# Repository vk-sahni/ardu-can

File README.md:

# Ardu-CAN

Ardu-CAN is a compact embedded-controller PCB design portfolio built in KiCad.
It brings together an STM32F412 MCU, CAN-bus interface circuitry, an inertial
sensor, power-protection and regulation circuits, and a custom board layout.

Explore the editable KiCad design, project libraries, engineering exports, and
3D assembly model below. The repository also documents the current design
review and next steps toward a fabrication release.

> **Board identity:** the PCB silkscreen currently says `Can-Glove-Node`.
> `Ardu-CAN` is the portfolio/project name used in this repository.

## Contents

- [Project objectives](#project-objectives)
- [Verified hardware features](#verified-hardware-features)
- [Hardware architecture](#hardware-architecture)
- [PCB design overview](#pcb-design-overview)
- [Schematic and engineering exports](#schematic-and-engineering-exports)
- [3D model](#3d-model)
- [Engineering review and release status](#engineering-review-and-release-status)
- [Open the project in KiCad](#open-the-project-in-kicad)
- [Commercial design services](#commercial-design-services)
- [Licensing and third-party assets](#licensing-and-third-party-assets)

## Project objectives

The project brings together an STM32 microcontroller, a CAN physical-layer
interface, an inertial measurement component, power input protection, and
connectors on a custom PCB. It demonstrates schematic capture, component and
footprint selection, board placement and routing, local KiCad library assets,
and 3D assembly export.

This portfolio focuses on the hardware design and its engineering assets.
Firmware and system-level behavior can be scoped separately for projects that
need them.

## Verified hardware features

The following parts and design elements were confirmed in the checked-in
schematic/PCB data and the KiCad BOM export:

| Design element | Verified implementation |
| --- | --- |
| Main MCU | U8, `STM32F412CGUx`, in a 48-pin QFN footprint |
| CAN physical layer | U5, `TJA1051TK-3` CAN transceiver; J1 and J2 are labeled `CAN` |
| CAN protection | D1 is `NUP2105L`; ESD9C3.3ST5G protection components also appear in the design |
| Inertial sensor | U4, `ICM-42688-P` |
| 3.3 V regulator | U6, `NCV8705MT33TCG` |
| Input protection | U1, `LM66100DCK`, on the reverse-polarity-protection sheet |
| Clock component | X1, `LFSPXO072801REEL` |
| Connections | JST GH/SH connectors and headers, including two 4-pin connectors labeled `CAN` |
| Test access | Three test-point footprints are present in the exported BOM |

The STM32F412 family datasheet lists an on-chip bxCAN controller
([STMicroelectronics datasheet](https://www.st.com/resource/en/datasheet/stm32f412cg.pdf));
U5 is the separate TJA1051 physical-layer transceiver. The schematic therefore
contains both controller-capable MCU hardware and a CAN transceiver, but the
repository has no firmware or test evidence establishing bus operation,
bit-rate, termination behavior, or protocol-level performance.

The schematic also contains passives, fuses, LEDs, and other protection
components. Part ratings, exact connector pin assignments, supported CAN
bit-rates, sensor configuration, and system behavior must be confirmed against
the detailed design and component datasheets before use.

## Hardware architecture

The KiCad schematic is organized into these sheets:

- `REVERSE_POLARITY_PROTECTION`
- `POWER_SUPPLY`
- `3.3_REGULATOR`
- `STM32`
- `CAN_DRIVER`
- `Accel`
- `CONNECTORS`

The exported schematic PDF includes the hierarchy page and all seven circuit
sheets. Current electrical review findings are summarized in the validation
section below.

## PCB design overview

- Nominal board outline: **37 × 37 mm**, as drawn on `Edge.Cuts`.
- Configured board thickness: **1.6 mm**.
- Configured copper stackup: **six copper layers** (front, four inner layers,
  and back).
- The outline contains four circular, nominal 3 mm diameter `Edge.Cuts`
  features. Confirm their intended use and mechanical clearances in the final
  enclosure and fabrication review.
- The source PCB contains 82 footprints and routed copper. This count is from
  the board file and is not an assembly or production status.

## Schematic and engineering exports

The schematic illustration below shows the actual KiCad CAN-driver sheet with
a summary of other verified blocks. For readable circuit detail, use the full
PDF rather than relying on the thumbnail.

- [Full eight-page schematic PDF](docs/ardu-can-schematic.pdf)
- [KiCad-exported BOM CSV](docs/ardu-can-bom.csv)
- Editable root schematic: [`ardu-can.kicad_sch`](ardu-can.kicad_sch)
- Editable board: [`ardu-can.kicad_pcb`](ardu-can.kicad_pcb)
- KiCad project settings: [`ardu-can.kicad_pro`](ardu-can.kicad_pro)
- Project symbol/footprint tables: [`sym-lib-table`](sym-lib-table) and
  [`fp-lib-table`](fp-lib-table)
- Custom and supporting KiCad libraries: [`lib/`](lib/)
- Component 3D models used by the project: [`model/`](model/)

The CSV is an exported design BOM, not a fully sourced purchasing BOM: supplier
part numbers, lifecycle checks, alternates, and procurement verification are
not established by that export.

## 3D model

The repository includes a KiCad-generated STEP assembly model. The image below
shows KiCad renders from multiple board views; it is not a photograph of a
fabricated or assembled unit.

- [Assembly STEP model](3d/ardu-can-assembly.step)
- [KiCad component model assets](model/)

The STEP file is an export of the current design data. No independent
mechanical fit, enclosure, or third-party CAD validation is claimed.

## Engineering review and release status

The project has editable KiCad design files and exported engineering assets.
Use the validation review to plan the next engineering steps before fabrication.

<details>
<summary>View current ERC/DRC findings and release checks</summary>

- The KiCad 10.0.6 PCB DRC reports **458 violations**, including via diameter
  and annular-width findings, library-footprint mismatches, clearance and
  copper-to-edge findings, silkscreen/courtyard issues, dangling tracks, and
  one unconnected item.
- The schematic ERC reports **61 violations**: 11 errors and 50 warnings.
  Findings include hierarchical sheet-pin/label mismatches, undriven power
  pins, and pin-type warnings.
- The source includes project-specific symbol and footprint tables, but the
  current checks still report footprint-library association/mismatch issues.
- No Gerber, drill, pick-and-place, or fabrication job output files are
  included.
- No fabricated-board, assembly, electrical bench test, or firmware validation
  evidence is included.

The detailed [design review](docs/design-review.md), [PCB DRC report](docs/pcb-drc-report.txt),
and [schematic ERC report](docs/schematic-erc-report.txt) provide the exact
findings. The release workflow is to resolve and rerun ERC/DRC, verify library
associations and footprint assignments, check the outline, holes, connector
mating clearances, enclosure fit, stack-up, and fabricator capabilities, then
generate and inspect Gerber/drill outputs and complete a sourced BOM as needed.

</details>

## Open the project in KiCad

1. Use **KiCad 10** (the checked CLI version for the exports and checks in this
   repository was 10.0.6).
2. Open `ardu-can.kicad_pro` from the repository root.
3. Open the root schematic or PCB editor from the project manager.
4. Keep the `lib/` and `model/` folders in their current relative locations:
   the project tables and footprints use project-relative library/model paths.
5. Review the current ERC/DRC findings before editing or preparing fabrication
   data.

Opening the project in another KiCad version may prompt a file-format upgrade.
Make a separate copy before accepting a project-wide upgrade.

## Commercial design services

This project is a portfolio example of the kinds of schematic, PCB layout,
component/footprint, and 3D STEP work available as a custom service. It does not
establish that every feature in a future client design is included, tested, or
certified.

The service scope, revision allowance, source files, manufacturing outputs,
firmware, and testing are defined per project and agreed package. Fabrication,
assembly, firmware development, and physical testing are not included unless
explicitly agreed.

See the [Fiverr listing and packages](docs/fiverr-gig.md) for service details.

## Licensing and third-party assets

No blanket project license is included because the repository combines original
design files with library/model assets that may have separate license terms.
The ICM-42688-P library folder includes its own `License.txt`; retain and review
third-party notices before redistribution or commercial reuse. Agree ownership
and licensing for client deliverables in writing before work begins.

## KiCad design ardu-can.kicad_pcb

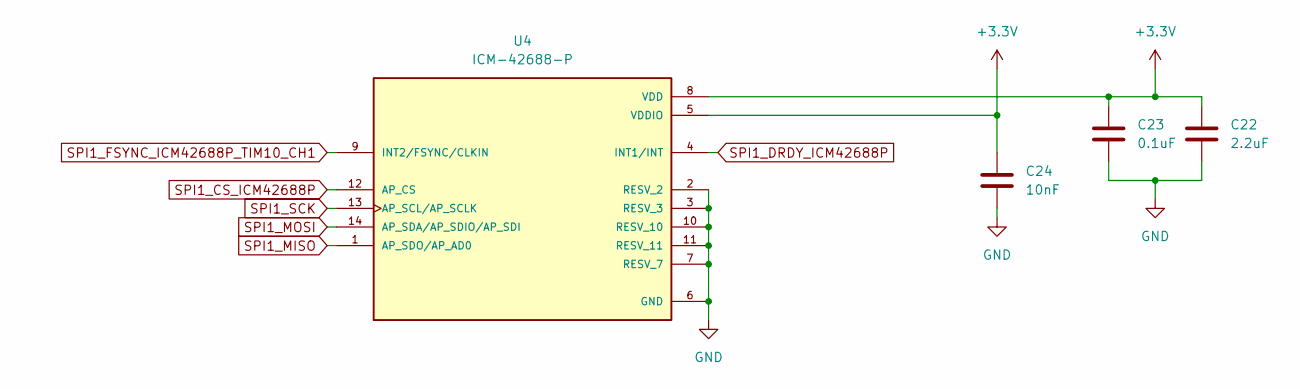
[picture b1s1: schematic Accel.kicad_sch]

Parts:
C22: 2.2uF; C_0603_1608Metric_Pad1.08x0.95mm_HandSolder
C23: 0.1uF; C_0603_1608Metric_Pad1.08x0.95mm_HandSolder
C24: 10nF; C_0603_1608Metric_Pad1.08x0.95mm_HandSolder
U4: ICM-42688-P; PQFN50P300X250X97-14N; PARTREV 1.2

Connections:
+3.3V: C22.1, C23.1, C24.1, U4.5 (VDDIO), U4.8 (VDD); also elsewhere on the board
GND: C22.2, C23.2, C24.2, U4.2 (RESV_2), U4.3 (RESV_3), U4.6 (GND), U4.7 (RESV_7), U4.10 (RESV_10), U4.11 (RESV_11); also elsewhere on the board
SPI1_CS_ICM42688P: U4.12 (AP_CS); also elsewhere on the board
SPI1_DRDY_ICM42688P: U4.4 (INT1/INT); also elsewhere on the board
SPI1_FSYNC_ICM42688P_TIM10_CH1: U4.9 (INT2/FSYNC/CLKIN); also elsewhere on the board
SPI1_MISO: U4.1 (AP_SDO/AP_AD0); also elsewhere on the board
SPI1_MOSI: U4.14 (AP_SDA/AP_SDIO/AP_SDI); also elsewhere on the board
SPI1_SCK: U4.13 (AP_SCL/AP_SCLK); also elsewhere on the board

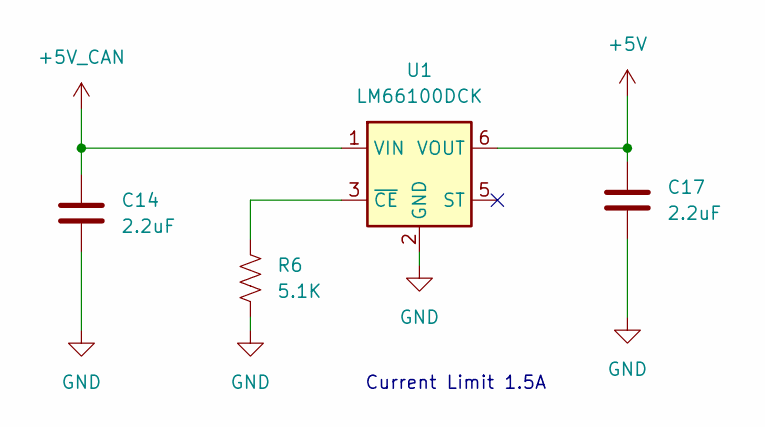
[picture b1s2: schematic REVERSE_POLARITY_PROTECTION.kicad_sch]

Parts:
C14, C17: 2.2uF; C_0603_1608Metric_Pad1.08x0.95mm_HandSolder
R6: 5.1K; R_0603_1608Metric_Pad0.98x0.95mm_HandSolder
U1: LM66100DCK; SOT-363_SC-70-6

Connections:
+5V: C17.1, U1.6 (VOUT); also elsewhere on the board
+5V_CAN: C14.1, U1.1 (VIN); also elsewhere on the board
GND: C14.2, C17.2, R6.2, U1.2 (GND); also elsewhere on the board
unnamed: R6.1, U1.3 (~CE)

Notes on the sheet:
Current Limit 1.5A

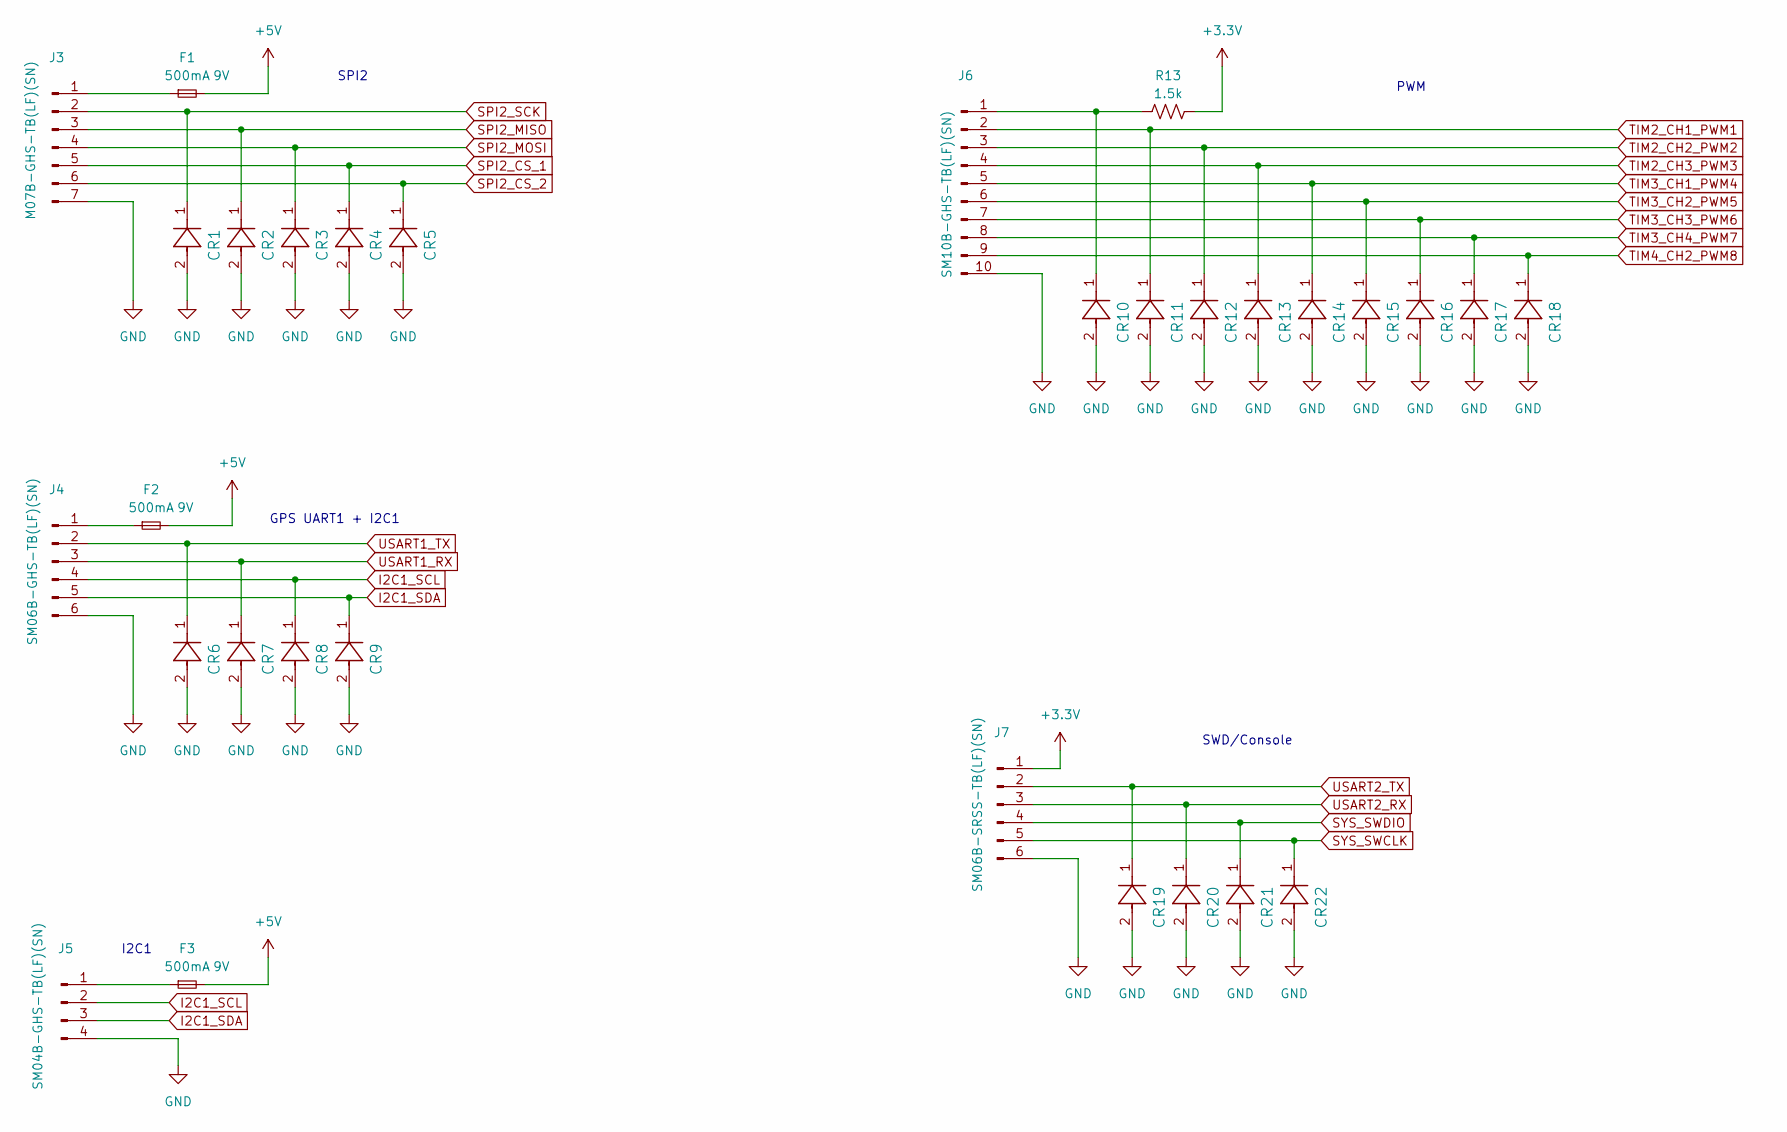
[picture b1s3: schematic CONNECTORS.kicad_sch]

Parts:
CR1, CR2, CR3, CR4, CR5, CR6, CR7, CR8, CR9, CR10, CR11, CR12, CR13, CR14, CR15, CR16, CR17, CR18, CR19, CR20, CR21, CR22: ESD9C3.3ST5G; CR_ESD9C3.3ST5G_ONS
F1, F2, F3: 500mA; Fuse_0603_1608Metric_Pad1.05x0.95mm_HandSolder
J3: M07B-GHS-TB(LF)(SN); JST_GH_SM07B-GHS-TB_1x07-1MP_P1.25mm_Horizontal
J4: SM06B-GHS-TB(LF)(SN); JST_GH_SM06B-GHS-TB_1x06-1MP_P1.25mm_Horizontal
J5: SM04B-GHS-TB(LF)(SN); JST_GH_SM04B-GHS-TB_1x04-1MP_P1.25mm_Horizontal
J6: SM10B-GHS-TB(LF)(SN); JST_GH_SM10B-GHS-TB_1x10-1MP_P1.25mm_Horizontal
J7: SM06B-SRSS-TB(LF)(SN); JST_SH_SM06B-SRSS-TB_1x06-1MP_P1.00mm_Horizontal
R13: 1.5k; R_0603_1608Metric_Pad0.98x0.95mm_HandSolder

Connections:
+3.3V: J7.1, R13.2; also elsewhere on the board
+5V: F1.2, F2.2, F3.2; also elsewhere on the board
GND: CR1.2, CR2.2, CR3.2, CR4.2, CR5.2, CR6.2, CR7.2, CR8.2, CR9.2, CR10.2, CR11.2, CR12.2, CR13.2, CR14.2, CR15.2, CR16.2, CR17.2, CR18.2, CR19.2, CR20.2, CR21.2, CR22.2, J3.7, J4.6, J5.4, J6.10, J7.6; also elsewhere on the board
I2C1_SCL: CR8.1, J4.4, J5.2; also elsewhere on the board
I2C1_SDA: CR9.1, J4.5, J5.3; also elsewhere on the board
unnamed: F1.1, J3.1
unnamed: F2.1, J4.1
unnamed: F3.1, J5.1
unnamed: CR10.1, J6.1, R13.1
SPI2_CS_1: CR4.1, J3.5; also elsewhere on the board
SPI2_CS_2: CR5.1, J3.6; also elsewhere on the board
SPI2_MISO: CR2.1, J3.3; also elsewhere on the board
SPI2_MOSI: CR3.1, J3.4; also elsewhere on the board
SPI2_SCK: CR1.1, J3.2; also elsewhere on the board
SYS_SWCLK: CR22.1, J7.5; also elsewhere on the board
SYS_SWDIO: CR21.1, J7.4; also elsewhere on the board
TIM2_CH1_PWM1: CR11.1, J6.2; also elsewhere on the board
TIM2_CH2_PWM2: CR12.1, J6.3; also elsewhere on the board
TIM2_CH3_PWM3: CR13.1, J6.4; also elsewhere on the board
TIM3_CH1_PWM4: CR14.1, J6.5; also elsewhere on the board
TIM3_CH2_PWM5: CR15.1, J6.6; also elsewhere on the board
TIM3_CH3_PWM6: CR16.1, J6.7; also elsewhere on the board
TIM3_CH4_PWM7: CR17.1, J6.8; also elsewhere on the board
TIM4_CH2_PWM8: CR18.1, J6.9; also elsewhere on the board
USART1_RX: CR7.1, J4.3; also elsewhere on the board
USART1_TX: CR6.1, J4.2; also elsewhere on the board
USART2_RX: CR20.1, J7.3; also elsewhere on the board
USART2_TX: CR19.1, J7.2; also elsewhere on the board

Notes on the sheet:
SPI2
SWD/Console
GPS UART1 + I2C1
I2C1
PWM

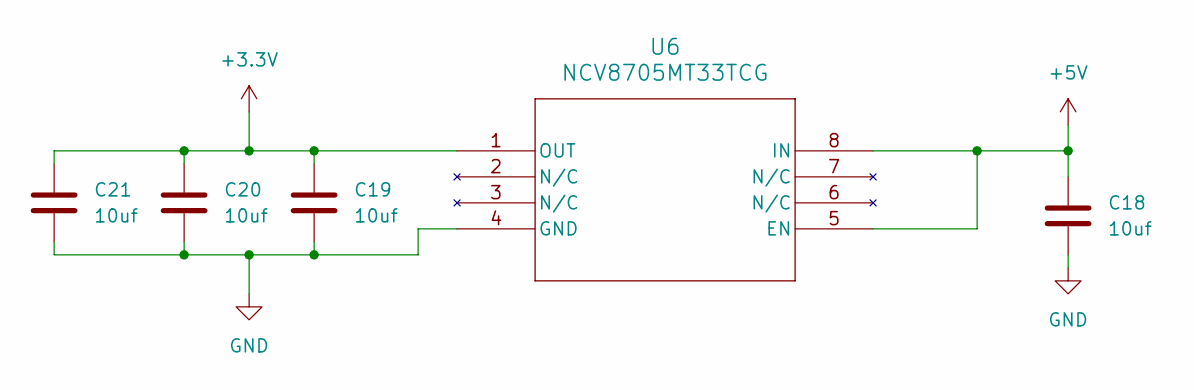
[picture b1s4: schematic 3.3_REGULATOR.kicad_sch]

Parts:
C18, C19, C20, C21: 10uf; C_0603_1608Metric_Pad1.08x0.95mm_HandSolder
U6: NCV8705MT33TCG; WDFN6_2X2_ONS

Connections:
+3.3V: C19.1, C20.1, C21.1, U6.1 (OUT); also elsewhere on the board
+5V: C18.1, U6.5 (EN), U6.8 (IN); also elsewhere on the board
GND: C18.2, C19.2, C20.2, C21.2, U6.4 (GND); also elsewhere on the board

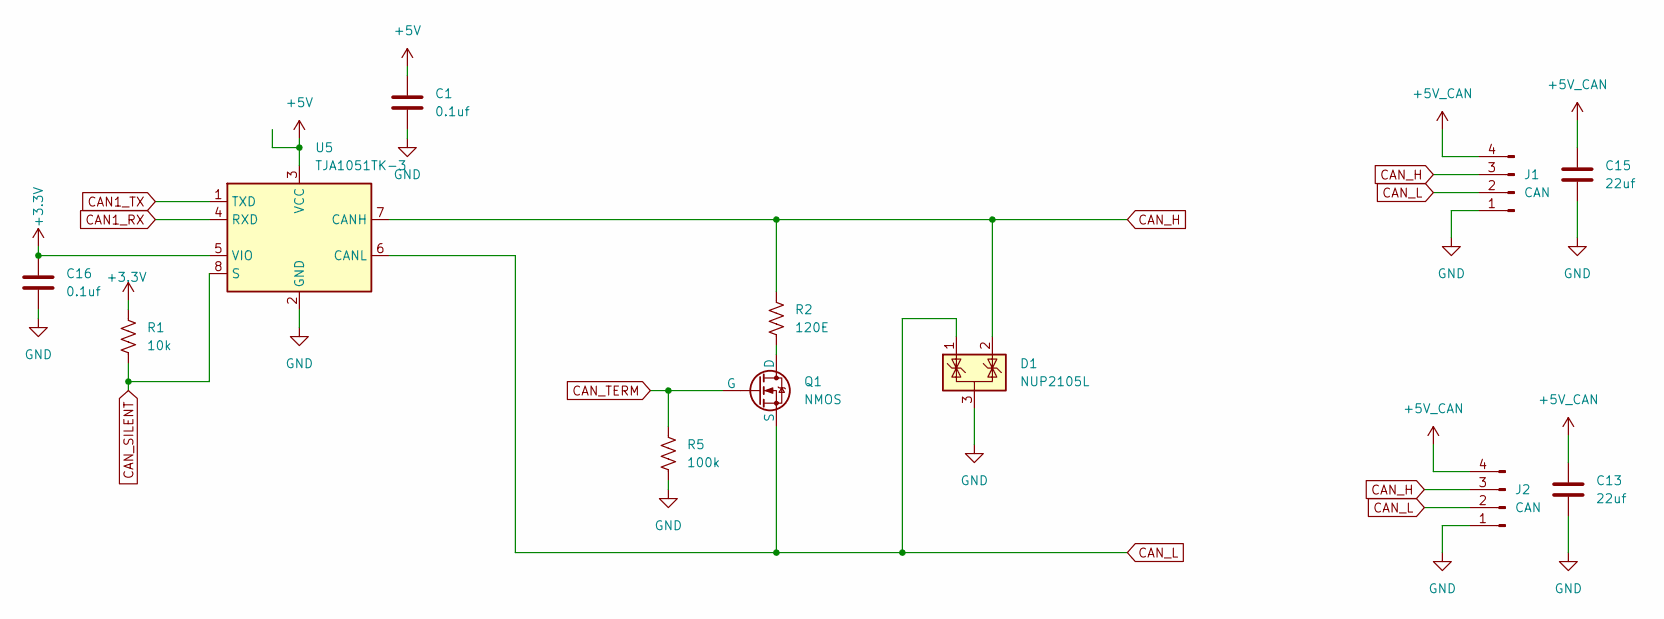
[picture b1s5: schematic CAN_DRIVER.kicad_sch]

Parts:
C1, C16: 0.1uf; C_0603_1608Metric_Pad1.08x0.95mm_HandSolder
C13, C15: 22uf; C_0603_1608Metric_Pad1.08x0.95mm_HandSolder
D1: NUP2105L; SOT-23
J1, J2: CAN; JST_GH_SM04B-GHS-TB_1x04-1MP_P1.25mm_Horizontal
Q1: NMOS; SOT-23_DIO
R1: 10k; R_0603_1608Metric_Pad0.98x0.95mm_HandSolder
R2: 120E; R_0603_1608Metric_Pad0.98x0.95mm_HandSolder
R5: 100k; R_0603_1608Metric_Pad0.98x0.95mm_HandSolder
U5: TJA1051TK-3; VSON-8-1EP_3x3mm_P0.65mm_EP1.6x2.4mm

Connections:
+3.3V: C16.1, R1.1, U5.5 (VIO); also elsewhere on the board
+5V: C1.1, U5.3 (VCC); also elsewhere on the board
+5V_CAN: C13.2, C15.2, J1.4, J2.4; also elsewhere on the board
CAN1_RX: U5.4 (RXD); also elsewhere on the board
CAN1_TX: U5.1 (TXD); also elsewhere on the board
CAN_H: D1.2 (K), J1.3, J2.3, R2.1, U5.7 (CANH)
CAN_L: D1.1 (K), J1.2, J2.2, Q1.3 (S), U5.6 (CANL)
CAN_SILENT: R1.2, U5.8 (S); also elsewhere on the board
CAN_TERM: Q1.2 (G), R5.1; also elsewhere on the board
GND: C1.2, C13.1, C15.1, C16.2, D1.3 (A), J1.1, J2.1, R5.2, U5.2 (GND), U5.9 (GND); also elsewhere on the board
unnamed: Q1.1 (D), R2.2

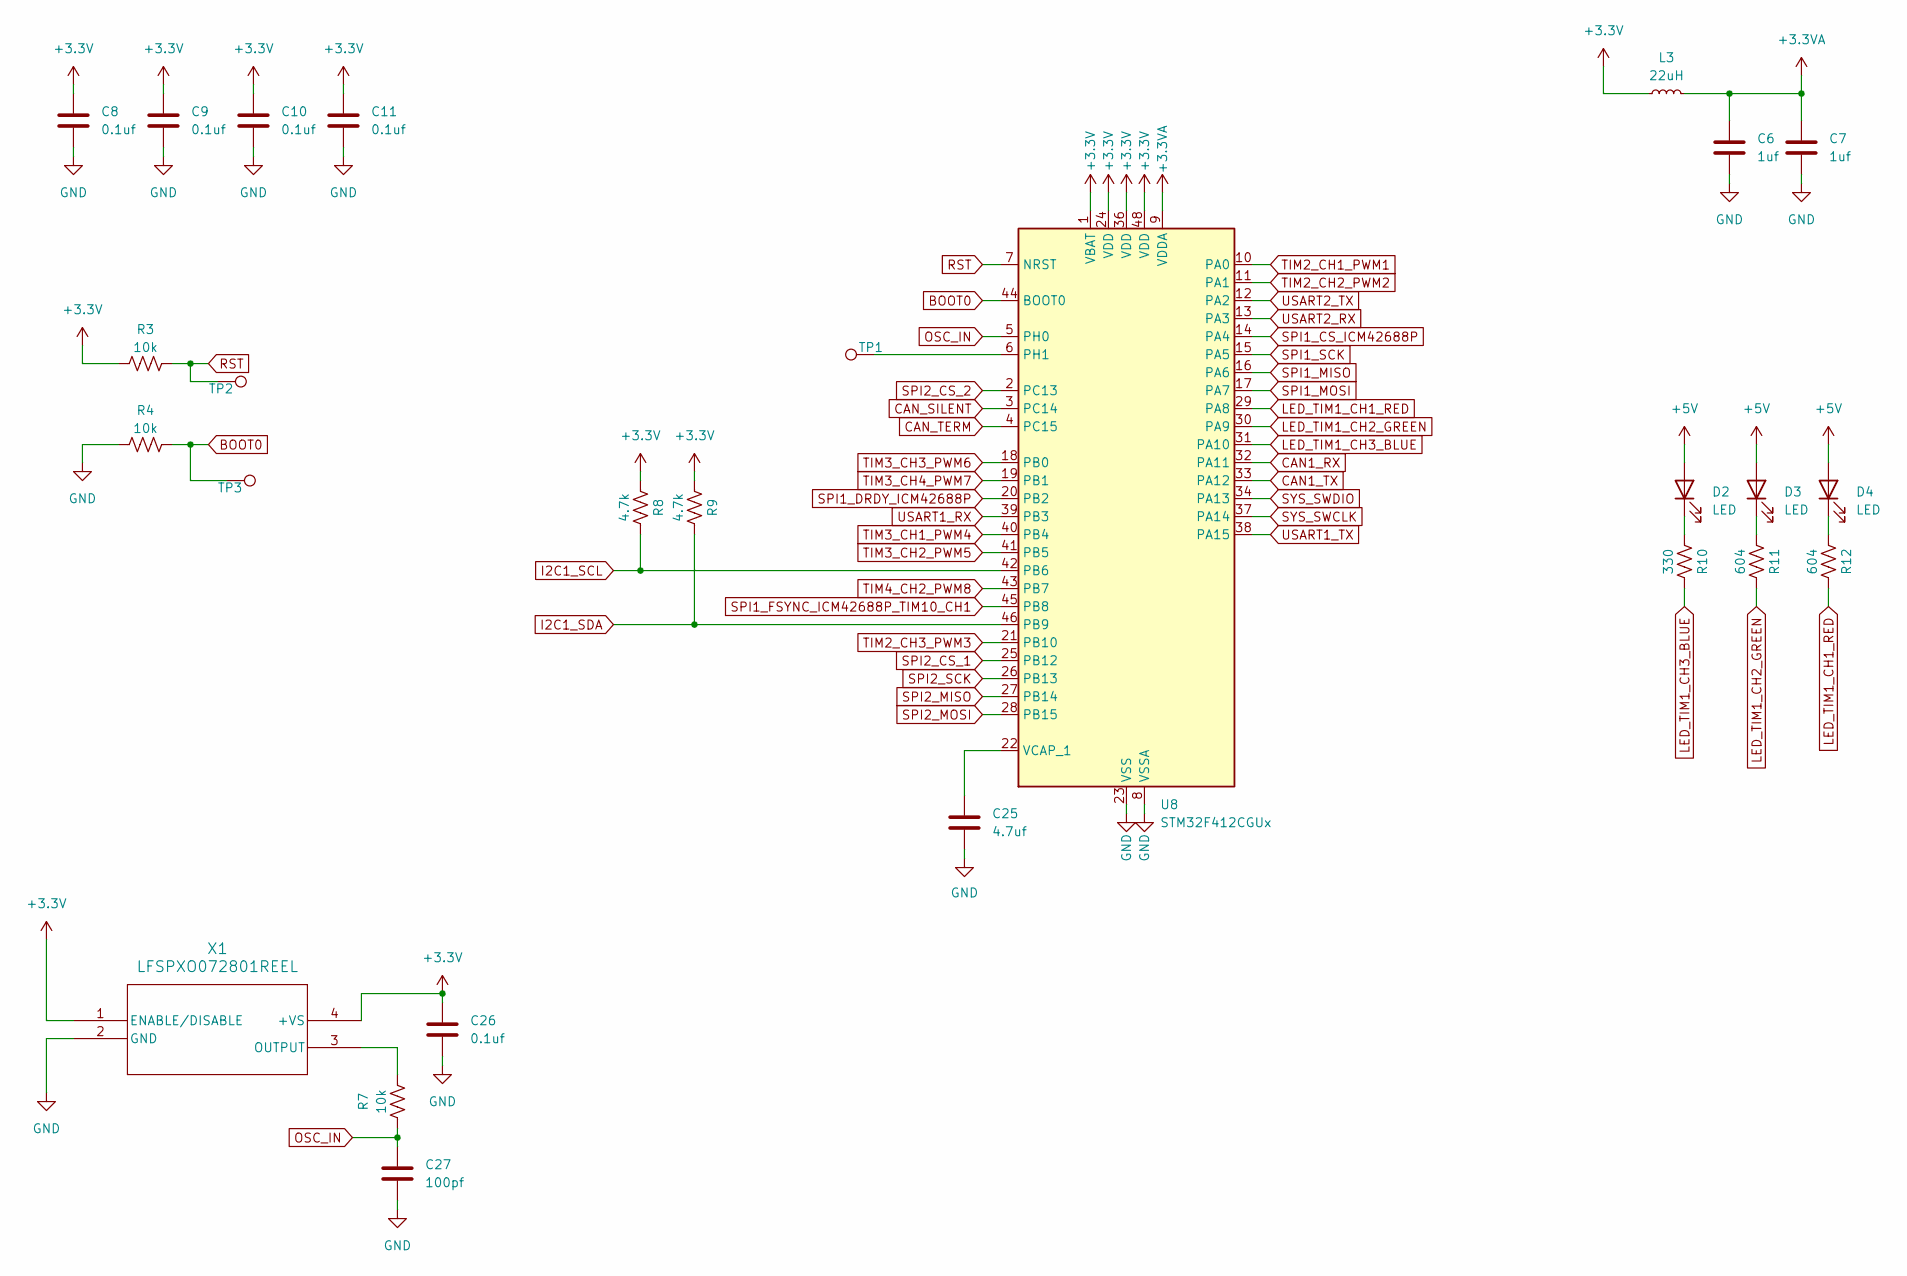
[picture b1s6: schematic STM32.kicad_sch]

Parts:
C6, C7: 1uf; C_0603_1608Metric_Pad1.08x0.95mm_HandSolder
C8, C9, C10, C11, C26: 0.1uf; C_0603_1608Metric_Pad1.08x0.95mm_HandSolder
C25: 4.7uf; C_0603_1608Metric_Pad1.08x0.95mm_HandSolder
C27: 100pf; C_0603_1608Metric_Pad1.08x0.95mm_HandSolder
D2, D3, D4: LED; LED_0603_1608Metric_Pad1.05x0.95mm_HandSolder
L3: 22uH; L_0603_1608Metric_Pad1.05x0.95mm_HandSolder
R3, R4, R7: 10k; R_0603_1608Metric_Pad0.98x0.95mm_HandSolder
R8, R9: 4.7k; R_0603_1608Metric_Pad0.98x0.95mm_HandSolder
R10: 330; R_0603_1608Metric_Pad0.98x0.95mm_HandSolder
R11, R12: 604; R_0603_1608Metric_Pad0.98x0.95mm_HandSolder
TP1, TP2, TP3: TestPoint; TestPoint_Pad_D1.0mm
U8: STM32F412CGUx; QFN-48-1EP_7x7mm_P0.5mm_EP5.6x5.6mm
X1: LFSPXO072801REEL; LFSPXO072801REEL_IQD

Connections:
+3.3V: C8.1, C9.1, C10.1, C11.1, C26.1, L3.1, R3.1, R8.2, R9.2, U8.1 (VBAT), U8.24 (VDD), U8.36 (VDD), U8.48 (VDD), X1.1 (ENABLE/DISABLE), X1.4 (+VS); also elsewhere on the board
+3.3VA: C6.1, C7.1, L3.2, U8.9 (VDDA)
+5V: D2.2 (A), D3.2 (A), D4.2 (A); also elsewhere on the board
BOOT0: R4.2, TP3.1, U8.44 (BOOT0)
CAN1_RX: U8.32 (PA11); also elsewhere on the board
CAN1_TX: U8.33 (PA12); also elsewhere on the board
CAN_SILENT: U8.3 (PC14); also elsewhere on the board
CAN_TERM: U8.4 (PC15); also elsewhere on the board
GND: C6.2, C7.2, C8.2, C9.2, C10.2, C11.2, C25.2, C26.2, C27.2, R4.1, U8.8 (VSSA), U8.23 (VSS), U8.35 (VSS), U8.47 (VSS), U8.49 (VSS), X1.2 (GND); also elsewhere on the board
I2C1_SCL: R8.1, U8.42 (PB6); also elsewhere on the board
I2C1_SDA: R9.1, U8.46 (PB9); also elsewhere on the board
LED_TIM1_CH1_RED: R12.1, U8.29 (PA8)
LED_TIM1_CH2_GREEN: R11.1, U8.30 (PA9)
LED_TIM1_CH3_BLUE: R10.1, U8.31 (PA10)
unnamed: D2.1 (K), R10.2
unnamed: D3.1 (K), R11.2
unnamed: D4.1 (K), R12.2
unnamed: TP1.1, U8.6 (PH1)
unnamed: C25.1, U8.22 (VCAP_1)
unnamed: R7.2, X1.3 (OUTPUT)
OSC_IN: C27.1, R7.1, U8.5 (PH0)
RST: R3.2, TP2.1, U8.7 (NRST)
SPI1_CS_ICM42688P: U8.14 (PA4); also elsewhere on the board
SPI1_DRDY_ICM42688P: U8.20 (PB2); also elsewhere on the board
SPI1_FSYNC_ICM42688P_TIM10_CH1: U8.45 (PB8); also elsewhere on the board
SPI1_MISO: U8.16 (PA6); also elsewhere on the board
SPI1_MOSI: U8.17 (PA7); also elsewhere on the board
SPI1_SCK: U8.15 (PA5); also elsewhere on the board
SPI2_CS_1: U8.25 (PB12); also elsewhere on the board
SPI2_CS_2: U8.2 (PC13); also elsewhere on the board
SPI2_MISO: U8.27 (PB14); also elsewhere on the board
SPI2_MOSI: U8.28 (PB15); also elsewhere on the board
SPI2_SCK: U8.26 (PB13); also elsewhere on the board
SYS_SWCLK: U8.37 (PA14); also elsewhere on the board
SYS_SWDIO: U8.34 (PA13); also elsewhere on the board
TIM2_CH1_PWM1: U8.10 (PA0); also elsewhere on the board
TIM2_CH2_PWM2: U8.11 (PA1); also elsewhere on the board
TIM2_CH3_PWM3: U8.21 (PB10); also elsewhere on the board
TIM3_CH1_PWM4: U8.40 (PB4); also elsewhere on the board
TIM3_CH2_PWM5: U8.41 (PB5); also elsewhere on the board
TIM3_CH3_PWM6: U8.18 (PB0); also elsewhere on the board
TIM3_CH4_PWM7: U8.19 (PB1); also elsewhere on the board
TIM4_CH2_PWM8: U8.43 (PB7); also elsewhere on the board
USART1_RX: U8.39 (PB3); also elsewhere on the board
USART1_TX: U8.38 (PA15); also elsewhere on the board
USART2_RX: U8.13 (PA3); also elsewhere on the board
USART2_TX: U8.12 (PA2); also elsewhere on the board

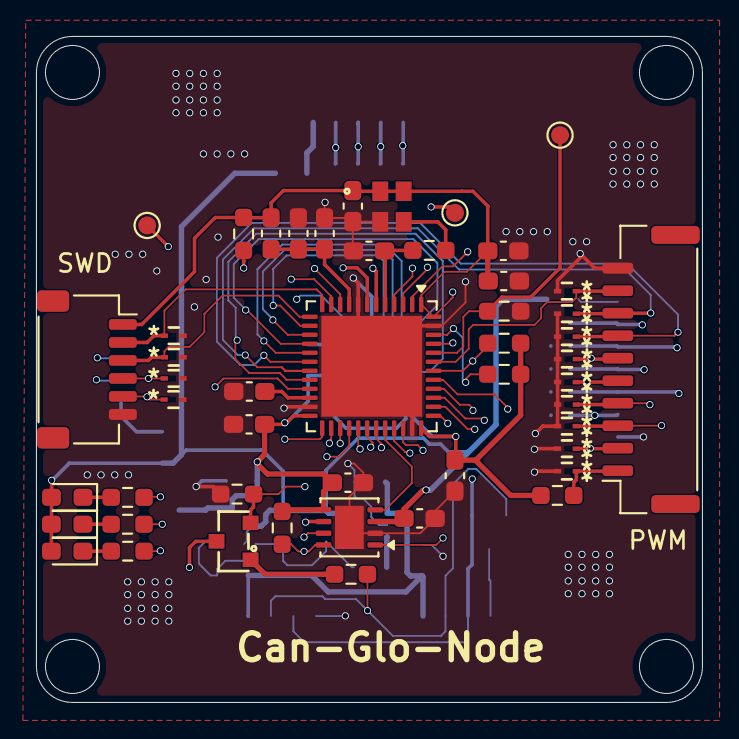
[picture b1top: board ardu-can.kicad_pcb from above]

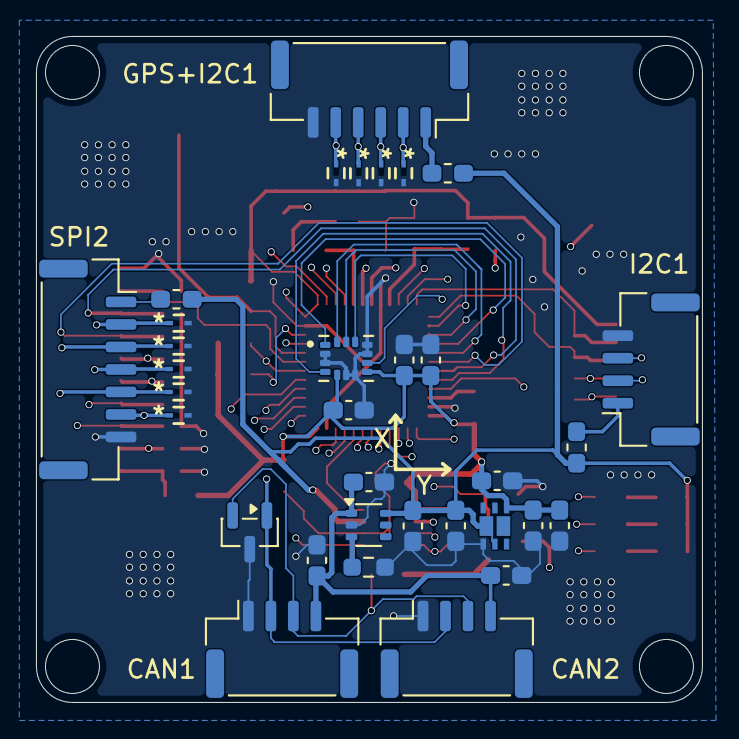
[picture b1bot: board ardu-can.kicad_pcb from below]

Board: 6 copper layers, 37.0 x 37.0 mm, 82 parts (33 on the bottom side), 56 nets.

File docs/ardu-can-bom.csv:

"Refs","Value","Footprint","Qty","DNP"
"C1","0.1uf","Capacitor_SMD:C_0603_1608Metric_Pad1.08x0.95mm_HandSolder","1",""
"C6","1uf","Capacitor_SMD:C_0603_1608Metric_Pad1.08x0.95mm_HandSolder","1",""
"C7","1uf","Capacitor_SMD:C_0603_1608Metric_Pad1.08x0.95mm_HandSolder","1",""
"C8","0.1uf","Capacitor_SMD:C_0603_1608Metric_Pad1.08x0.95mm_HandSolder","1",""
"C9","0.1uf","Capacitor_SMD:C_0603_1608Metric_Pad1.08x0.95mm_HandSolder","1",""
"C10","0.1uf","Capacitor_SMD:C_0603_1608Metric_Pad1.08x0.95mm_HandSolder","1",""
"C11","0.1uf","Capacitor_SMD:C_0603_1608Metric_Pad1.08x0.95mm_HandSolder","1",""
"C13","22uf","Capacitor_SMD:C_0603_1608Metric_Pad1.08x0.95mm_HandSolder","1",""
"C14","2.2uF","Capacitor_SMD:C_0603_1608Metric_Pad1.08x0.95mm_HandSolder","1",""
"C15","22uf","Capacitor_SMD:C_0603_1608Metric_Pad1.08x0.95mm_HandSolder","1",""
"C16","0.1uf","Capacitor_SMD:C_0603_1608Metric_Pad1.08x0.95mm_HandSolder","1",""
"C17","2.2uF","Capacitor_SMD:C_0603_1608Metric_Pad1.08x0.95mm_HandSolder","1",""
"C18","10uf","Capacitor_SMD:C_0603_1608Metric_Pad1.08x0.95mm_HandSolder","1",""
"C19","10uf","Capacitor_SMD:C_0603_1608Metric_Pad1.08x0.95mm_HandSolder","1",""
"C20","10uf","Capacitor_SMD:C_0603_1608Metric_Pad1.08x0.95mm_HandSolder","1",""
"C21","10uf","Capacitor_SMD:C_0603_1608Metric_Pad1.08x0.95mm_HandSolder","1",""
"C22","2.2uF","Capacitor_SMD:C_0603_1608Metric_Pad1.08x0.95mm_HandSolder","1",""
"C23","0.1uF","Capacitor_SMD:C_0603_1608Metric_Pad1.08x0.95mm_HandSolder","1",""
"C24","10nF","Capacitor_SMD:C_0603_1608Metric_Pad1.08x0.95mm_HandSolder","1",""
"C25","4.7uf","Capacitor_SMD:C_0603_1608Metric_Pad1.08x0.95mm_HandSolder","1",""
"C26","0.1uf","Capacitor_SMD:C_0603_1608Metric_Pad1.08x0.95mm_HandSolder","1",""
"C27","100pf","Capacitor_SMD:C_0603_1608Metric_Pad1.08x0.95mm_HandSolder","1",""
"CR1","ESD9C3.3ST5G","ESD9C3.3ST5G:CR_ESD9C3.3ST5G_ONS","1",""
"CR2","ESD9C3.3ST5G","ESD9C3.3ST5G:CR_ESD9C3.3ST5G_ONS","1",""
"CR3","ESD9C3.3ST5G","ESD9C3.3ST5G:CR_ESD9C3.3ST5G_ONS","1",""
"CR4","ESD9C3.3ST5G","ESD9C3.3ST5G:CR_ESD9C3.3ST5G_ONS","1",""
"CR5","ESD9C3.3ST5G","ESD9C3.3ST5G:CR_ESD9C3.3ST5G_ONS","1",""
"CR6","ESD9C3.3ST5G","ESD9C3.3ST5G:CR_ESD9C3.3ST5G_ONS","1",""
"CR7","ESD9C3.3ST5G","ESD9C3.3ST5G:CR_ESD9C3.3ST5G_ONS","1",""
"CR8","ESD9C3.3ST5G","ESD9C3.3ST5G:CR_ESD9C3.3ST5G_ONS","1",""
"CR9","ESD9C3.3ST5G","ESD9C3.3ST5G:CR_ESD9C3.3ST5G_ONS","1",""
"CR10","ESD9C3.3ST5G","ESD9C3.3ST5G:CR_ESD9C3.3ST5G_ONS","1",""
"CR11","ESD9C3.3ST5G","ESD9C3.3ST5G:CR_ESD9C3.3ST5G_ONS","1",""
"CR12","ESD9C3.3ST5G","ESD9C3.3ST5G:CR_ESD9C3.3ST5G_ONS","1",""
"CR13","ESD9C3.3ST5G","ESD9C3.3ST5G:CR_ESD9C3.3ST5G_ONS","1",""
"CR14","ESD9C3.3ST5G","ESD9C3.3ST5G:CR_ESD9C3.3ST5G_ONS","1",""
"CR15","ESD9C3.3ST5G","ESD9C3.3ST5G:CR_ESD9C3.3ST5G_ONS","1",""
"CR16","ESD9C3.3ST5G","ESD9C3.3ST5G:CR_ESD9C3.3ST5G_ONS","1",""
"CR17","ESD9C3.3ST5G","ESD9C3.3ST5G:CR_ESD9C3.3ST5G_ONS","1",""
"CR18","ESD9C3.3ST5G","ESD9C3.3ST5G:CR_ESD9C3.3ST5G_ONS","1",""
"CR19","ESD9C3.3ST5G","ESD9C3.3ST5G:CR_ESD9C3.3ST5G_ONS","1",""
"CR20","ESD9C3.3ST5G","ESD9C3.3ST5G:CR_ESD9C3.3ST5G_ONS","1",""
"CR21","ESD9C3.3ST5G","ESD9C3.3ST5G:CR_ESD9C3.3ST5G_ONS","1",""
"CR22","ESD9C3.3ST5G","ESD9C3.3ST5G:CR_ESD9C3.3ST5G_ONS","1",""
"D1","NUP2105L","Package_TO_SOT_SMD:SOT-23","1",""
"D2","LED","LED_SMD:LED_0603_1608Metric_Pad1.05x0.95mm_HandSolder","1",""
"D3","LED","LED_SMD:LED_0603_1608Metric_Pad1.05x0.95mm_HandSolder","1",""
"D4","LED","LED_SMD:LED_0603_1608Metric_Pad1.05x0.95mm_HandSolder","1",""
"F1","500mA","Fuse:Fuse_0603_1608Metric_Pad1.05x0.95mm_HandSolder","1",""
"F2","500mA","Fuse:Fuse_0603_1608Metric_Pad1.05x0.95mm_HandSolder","1",""
"F3","500mA","Fuse:Fuse_0603_1608Metric_Pad1.05x0.95mm_HandSolder","1",""
"J1","CAN","Connector_JST:JST_GH_SM04B-GHS-TB_1x04-1MP_P1.25mm_Horizontal","1",""
"J2","CAN","Connector_JST:JST_GH_SM04B-GHS-TB_1x04-1MP_P1.25mm_Horizontal","1",""
"J3","M07B-GHS-TB(LF)(SN)","Connector_JST:JST_GH_SM07B-GHS-TB_1x07-1MP_P1.25mm_Horizontal","1",""
"J4","SM06B-GHS-TB(LF)(SN)","Connector_JST:JST_GH_SM06B-GHS-TB_1x06-1MP_P1.25mm_Horizontal","1",""
"J5","SM04B-GHS-TB(LF)(SN)","Connector_JST:JST_GH_SM04B-GHS-TB_1x04-1MP_P1.25mm_Horizontal","1",""
"J6","SM10B-GHS-TB(LF)(SN)","Connector_JST:JST_GH_SM10B-GHS-TB_1x10-1MP_P1.25mm_Horizontal","1",""
"J7","SM06B-SRSS-TB(LF)(SN)","Connector_JST:JST_SH_SM06B-SRSS-TB_1x06-1MP_P1.00mm_Horizontal","1",""
"L3","22uH","Inductor_SMD:L_0603_1608Metric_Pad1.05x0.95mm_HandSolder","1",""
"Q1","NMOS","DMN53D0L_7:SOT-23_DIO","1",""
"R1","10k","Resistor_SMD:R_0603_1608Metric_Pad0.98x0.95mm_HandSolder","1",""
"R2","120E","Resistor_SMD:R_0603_1608Metric_Pad0.98x0.95mm_HandSolder","1",""
"R3","10k","Resistor_SMD:R_0603_1608Metric_Pad0.98x0.95mm_HandSolder","1",""
"R4","10k","Resistor_SMD:R_0603_1608Metric_Pad0.98x0.95mm_HandSolder","1",""
"R5","100k","Resistor_SMD:R_0603_1608Metric_Pad0.98x0.95mm_HandSolder","1",""
"R6","5.1K","Resistor_SMD:R_0603_1608Metric_Pad0.98x0.95mm_HandSolder","1",""
"R7","10k","Resistor_SMD:R_0603_1608Metric_Pad0.98x0.95mm_HandSolder","1",""
"R8","4.7k","Resistor_SMD:R_0603_1608Metric_Pad0.98x0.95mm_HandSolder","1",""
"R9","4.7k","Resistor_SMD:R_0603_1608Metric_Pad0.98x0.95mm_HandSolder","1",""
"R10","330","Resistor_SMD:R_0603_1608Metric_Pad0.98x0.95mm_HandSolder","1",""
"R11","604","Resistor_SMD:R_0603_1608Metric_Pad0.98x0.95mm_HandSolder","1",""
"R12","604","Resistor_SMD:R_0603_1608Metric_Pad0.98x0.95mm_HandSolder","1",""
"R13","1.5k","Resistor_SMD:R_0603_1608Metric_Pad0.98x0.95mm_HandSolder","1",""
"TP1","TestPoint","TestPoint:TestPoint_Pad_D1.0mm","1",""
"TP2","TestPoint","TestPoint:TestPoint_Pad_D1.0mm","1",""
"TP3","TestPoint","TestPoint:TestPoint_Pad_D1.0mm","1",""
"U1","LM66100DCK","Package_TO_SOT_SMD:SOT-363_SC-70-6","1",""
"U4","ICM-42688-P","ICM-42688-P:PQFN50P300X250X97-14N","1",""
"U5","TJA1051TK-3","Package_SON:VSON-8-1EP_3x3mm_P0.65mm_EP1.6x2.4mm","1",""
"U6","NCV8705MT33TCG","footprints:WDFN6_2X2_ONS","1",""
"U8","STM32F412CGUx","Package_DFN_QFN:QFN-48-1EP_7x7mm_P0.5mm_EP5.6x5.6mm","1",""
"X1","LFSPXO072801REEL","LFSPXO072801REEL:LFSPXO072801REEL_IQD","1",""

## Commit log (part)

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2025-11-17 added ardu-can zip file
    It's a CAN driver module.
